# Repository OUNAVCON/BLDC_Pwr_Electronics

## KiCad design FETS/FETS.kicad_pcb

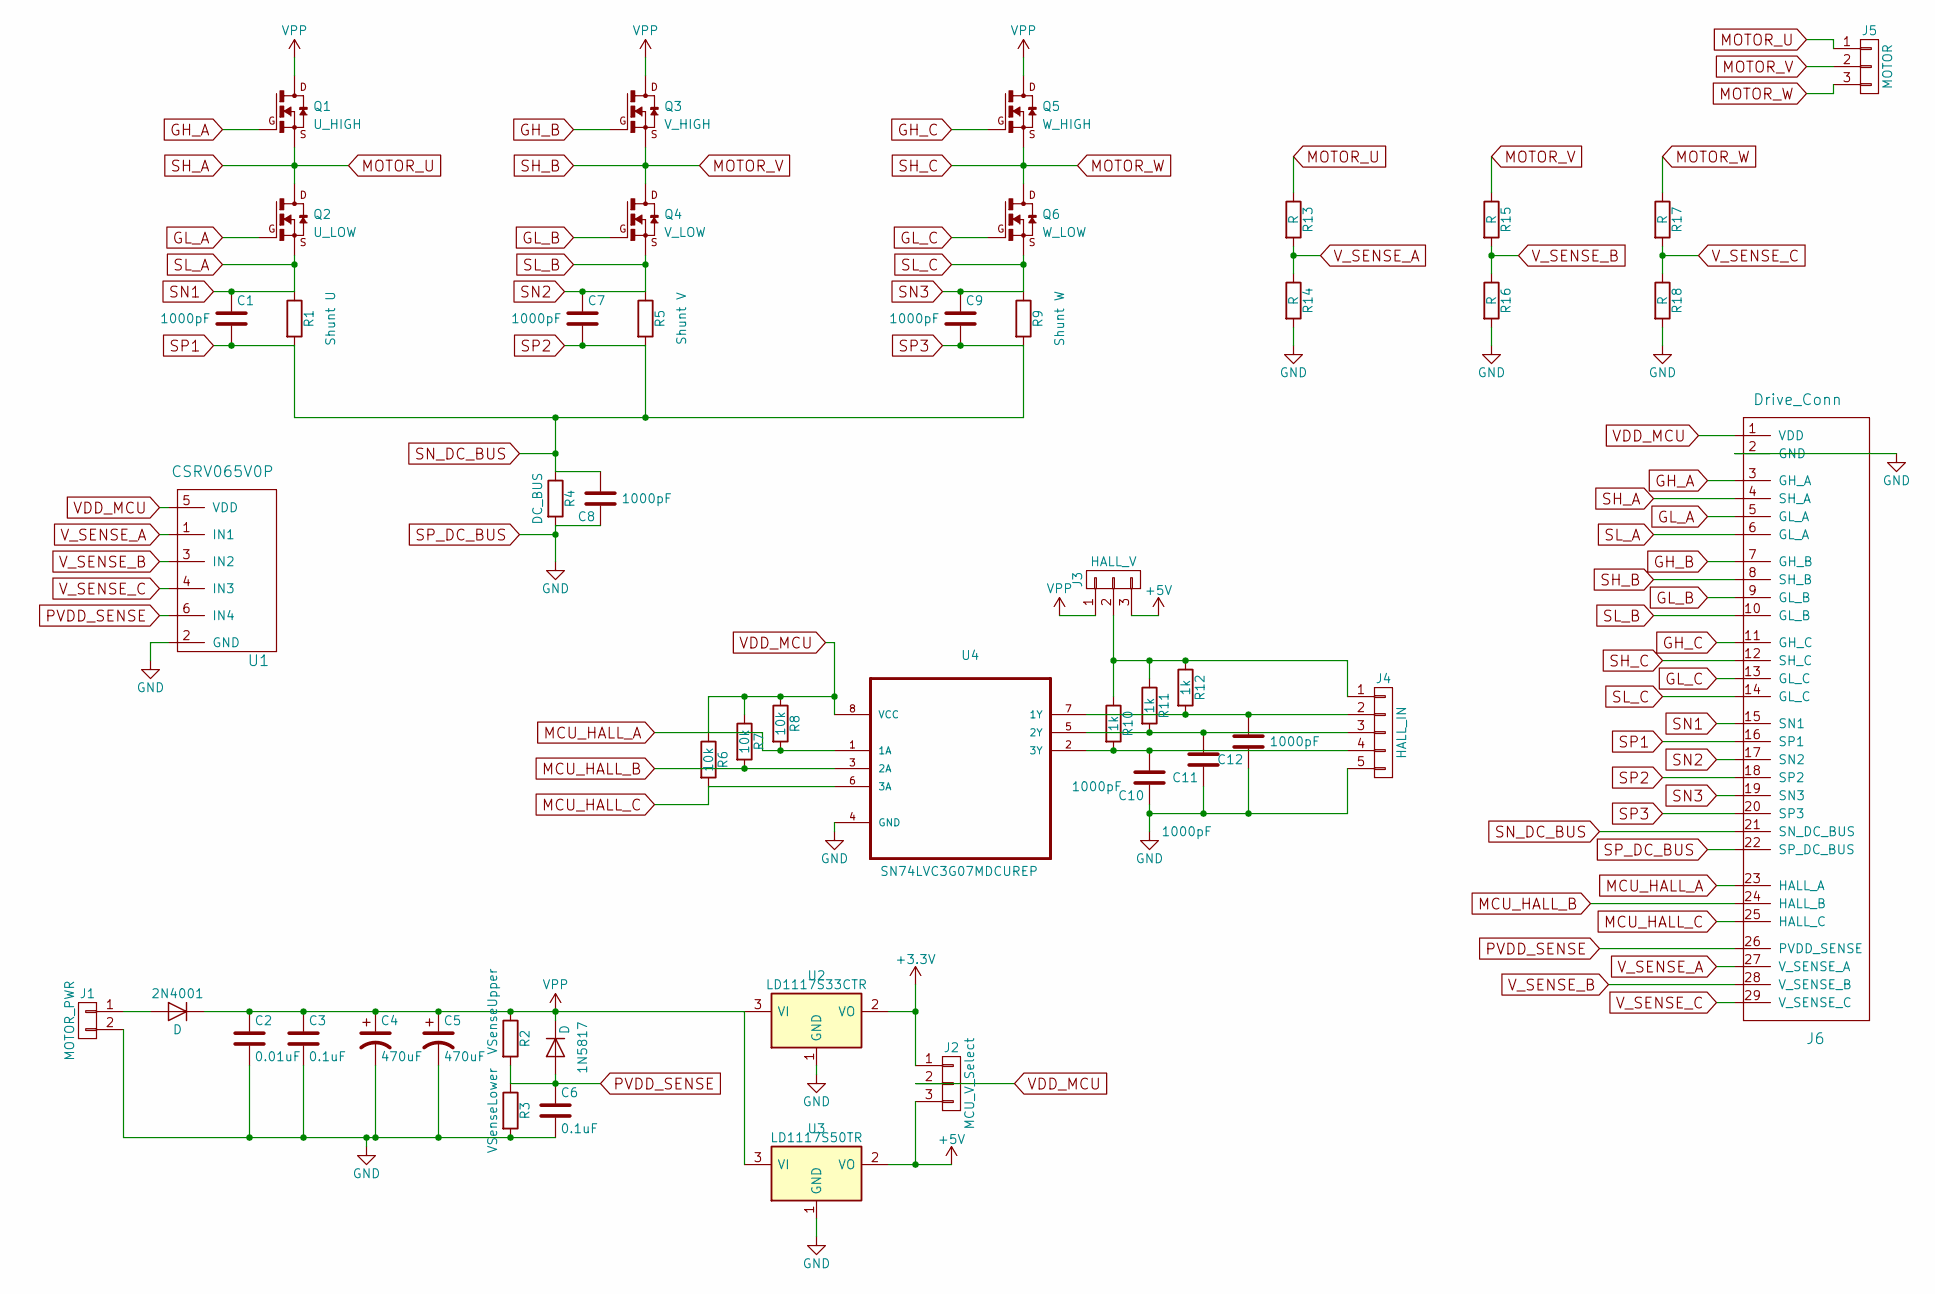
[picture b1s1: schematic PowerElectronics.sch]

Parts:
1N5817, 2N4001: D; D_SMA-SMB_Universal_Handsoldering
C1, C7, C8, C9, C10, C11, C12: 1000pF; C_1206_HandSoldering
C2: 0.01uF; C_1206_HandSoldering
C3, C6: 0.1uF; C_1206_HandSoldering
C4, C5: 470uF; CP_Elec_10x10.5
J1: MOTOR_PWR; Pin_Header_Straight_1x02_Pitch2.54mm
J2: MCU_V_Select; Pin_Header_Straight_1x03_Pitch2.54mm
J3: HALL_V; Pin_Header_Straight_1x03_Pitch2.54mm
J4: HALL_IN; Pin_Header_Straight_1x05_Pitch2.54mm
J5: MOTOR; Pin_Header_Straight_1x03_Pitch2.54mm
J6: Drive_Conn; Pin_Header_Straight_1x29_Pitch2.54mm
Q1: U_HIGH; LFPAK
Q2: U_LOW; LFPAK
Q3: V_HIGH; LFPAK
Q4: V_LOW; LFPAK
Q5: W_HIGH; LFPAK
Q6: W_LOW; LFPAK
R1: Shunt U; R_2512_HandSoldering
R2: VSenseUpper; R_1206_HandSoldering
R3: VSenseLower; R_1206_HandSoldering
R4: DC_BUS; R_2512_HandSoldering
R5: Shunt V; R_2512_HandSoldering
R6, R7, R8: 10k; R_1206_HandSoldering
R9: Shunt W; R_2512_HandSoldering
R10, R11, R12: 1k; R_1206_HandSoldering
R13, R14, R15, R16, R17, R18: R; R_1206_HandSoldering
U1: CSRV065V0P; SOT-363
U2: LD1117S33CTR; SOT-223
U3: LD1117S50TR; SOT-223
U4: SN74LVC3G07MDCUREP; SOP50P310X90-8N

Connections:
+3V3: J2.1, U2.2 (VO)
+5V: J2.3, J3.3, U3.2 (VO)
GH_A: J6.3 (GH_A), Q1.4 (G)
GH_B: J6.7 (GH_B), Q3.4 (G)
GH_C: J6.11 (GH_C), Q5.4 (G)
GL_A: J6.5 (GL_A), Q2.4 (G)
GL_B: J6.9 (GL_B), Q4.4 (G)
GL_C: J6.13 (GL_C), Q6.4 (G)
MCU_HALL_A: J6.23 (HALL_A), R8.2, U4.1 (1A)
MCU_HALL_B: J6.24 (HALL_B), R7.2, U4.3 (2A)
MCU_HALL_C: J6.25 (HALL_C), R6.2, U4.6 (3A)
MOTOR_U: J5.1, J6.4 (SH_A), Q1.1 (S), Q1.2 (S), Q1.3 (S), Q2.5 (D), R13.1
MOTOR_V: J5.2, J6.8 (SH_B), Q3.1 (S), Q3.2 (S), Q3.3 (S), Q4.5 (D), R15.1
MOTOR_W: J5.3, J6.12 (SH_C), Q5.1 (S), Q5.2 (S), Q5.3 (S), Q6.5 (D), R17.1
unnamed: 2N4001.2 (A), J1.1
unnamed: C10.2, J4.4, R10.2, U4.2 (3Y)
unnamed: C11.2, J4.3, R11.2, U4.5 (2Y)
unnamed: C12.2, J4.2, R12.2, U4.7 (1Y)
unnamed: J3.2, J4.1, R10.1, R11.1, R12.1
PVDD_SENSE: 1N5817.2 (A), C6.1, J6.26 (PVDD_SENSE), R2.2, R3.1, U1.6 (IN4)
SL_A: C1.1, J6.6 (GL_A), J6.15 (SN1), Q2.1 (S), Q2.2 (S), Q2.3 (S), R1.1
SL_B: C7.1, J6.10 (GL_B), J6.17 (SN2), Q4.1 (S), Q4.2 (S), Q4.3 (S), R5.1
SL_C: C9.1, J6.14 (GL_C), J6.19 (SN3), Q6.1 (S), Q6.2 (S), Q6.3 (S), R9.1
SN_DC_BUS: C1.2, C7.2, C8.2, C9.2, J6.16 (SP1), J6.18 (SP2), J6.20 (SP3), J6.21 (SN_DC_BUS), R1.2, R4.1, R5.2, R9.2
SP_DC_BUS: C2.2, C3.2, C4.2, C5.2, C6.2, C8.1, C10.1, C11.1, C12.1, J1.2, J4.5, J6.2 (GND), J6.22 (SP_DC_BUS), R3.2, R4.2, R14.2, R16.2, R18.2, U1.2 (GND), U2.1 (GND), U3.1 (GND), U4.4 (GND)
VDD_MCU: J2.2, J6.1 (VDD), R6.1, R7.1, R8.1, U1.5 (VDD), U4.8 (VCC)
VPP: 1N5817.1 (K), 2N4001.1 (K), C2.1, C3.1, C4.1, C5.1, J3.1, Q1.5 (D), Q3.5 (D), Q5.5 (D), R2.1, U2.3 (VI), U3.3 (VI)
V_SENSE_A: J6.27 (V_SENSE_A), R13.2, R14.1, U1.1 (IN1)
V_SENSE_B: J6.28 (V_SENSE_B), R15.2, R16.1, U1.3 (IN2)
V_SENSE_C: J6.29 (V_SENSE_C), R17.2, R18.1, U1.4 (IN3)

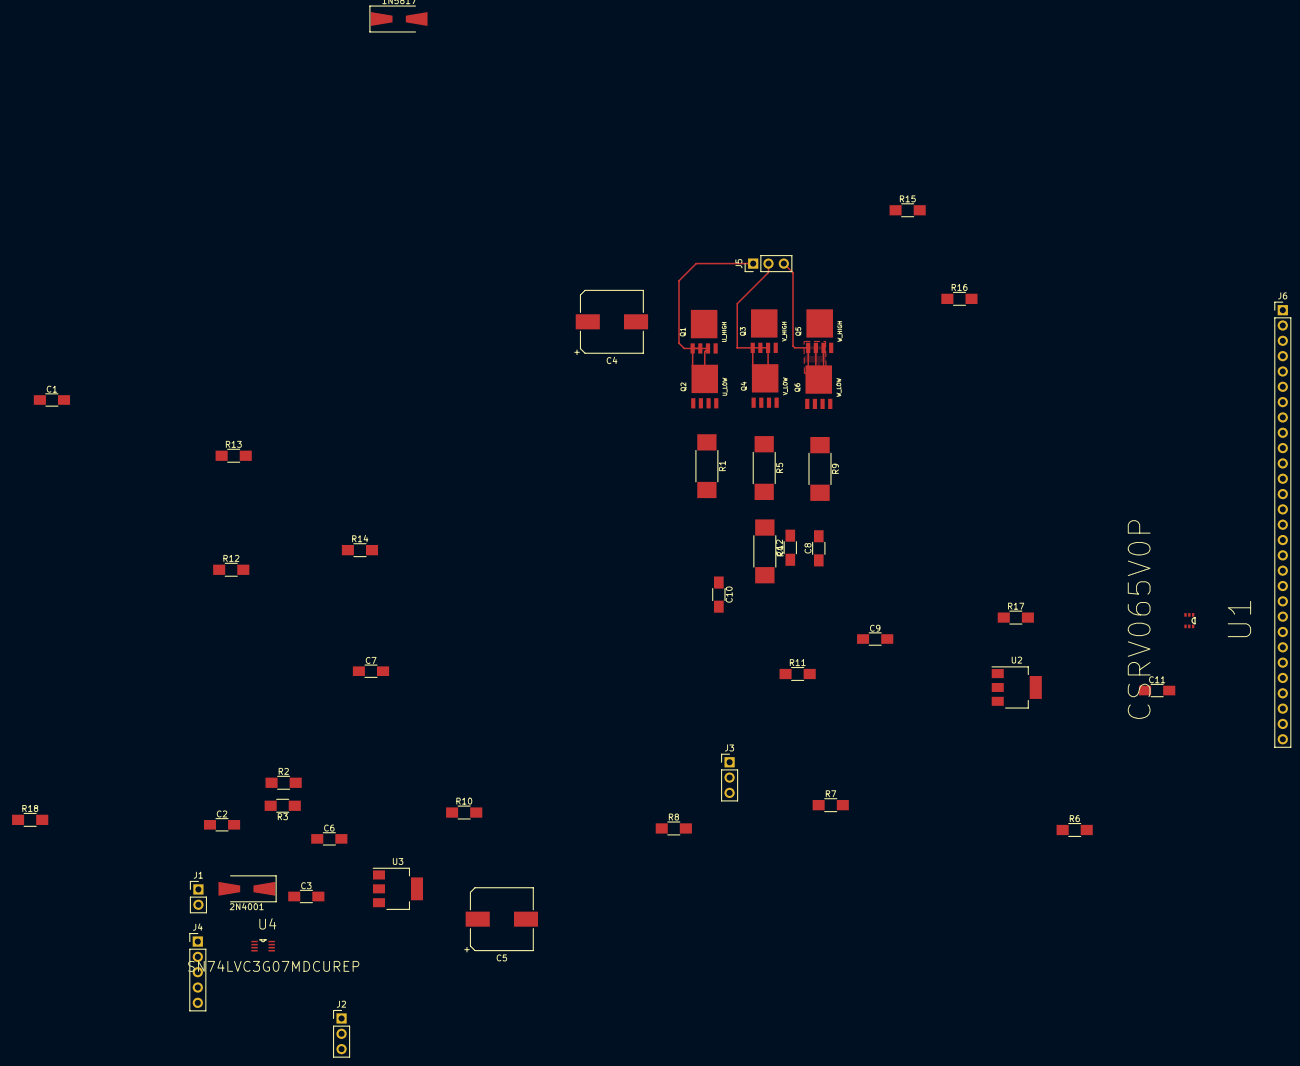
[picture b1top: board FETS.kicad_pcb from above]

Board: 2 copper layers, 48 parts (0 on the bottom side), 30 nets.

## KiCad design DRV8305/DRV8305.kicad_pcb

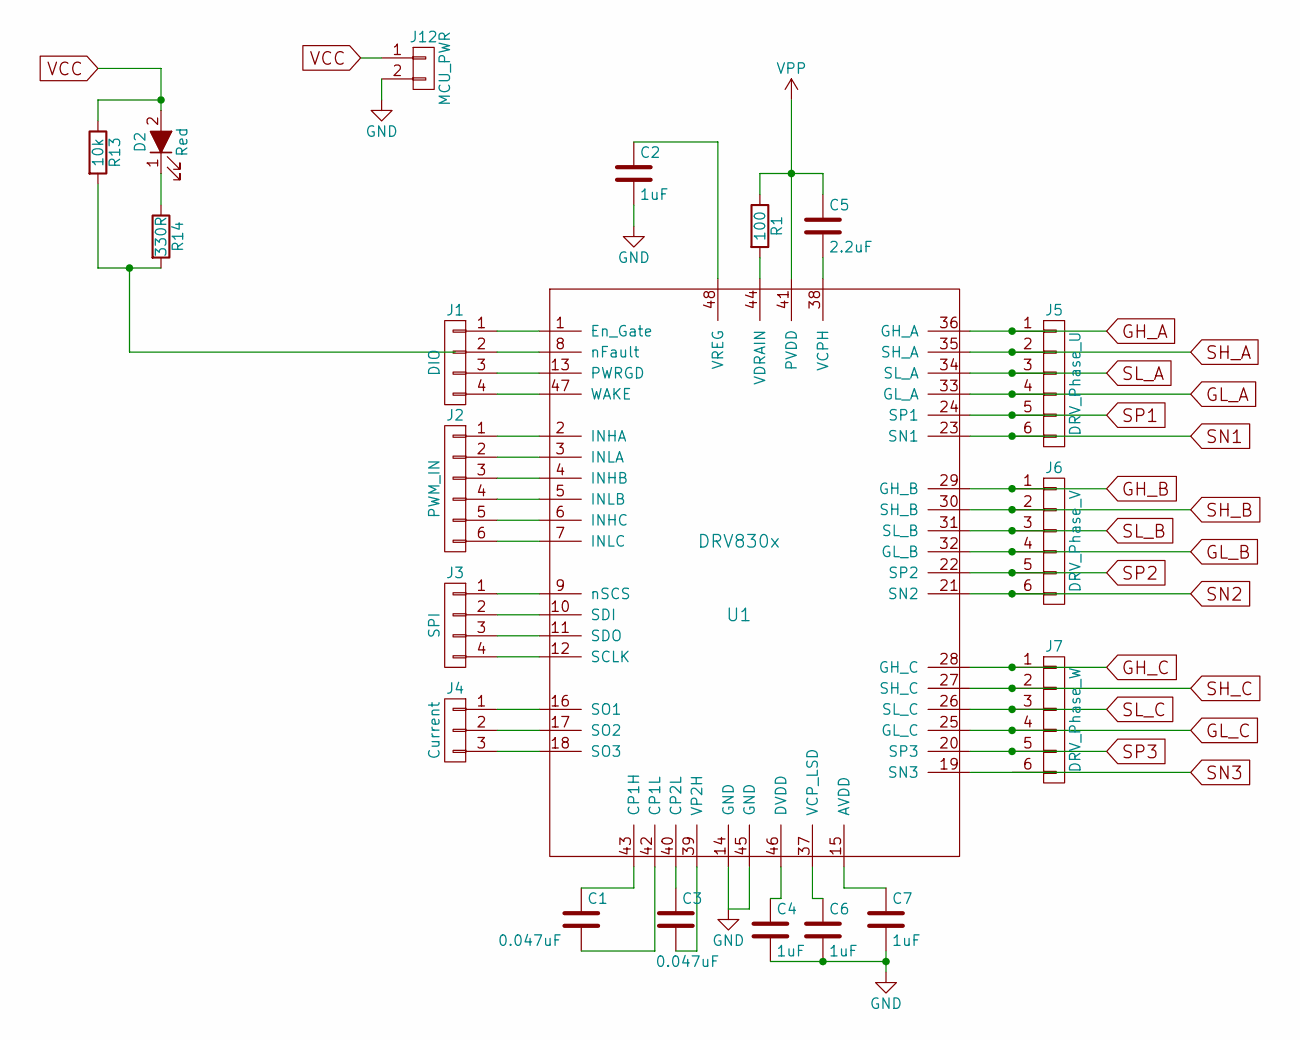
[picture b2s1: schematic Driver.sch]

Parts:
C1, C3: 0.047uF; C_1206_HandSoldering
C2, C4, C6, C7: 1uF; C_1206_HandSoldering
C5: 2.2uF; C_1206_HandSoldering
D2: Red; LED_1206_HandSoldering
J1: DIO; Pin_Header_Straight_1x04_Pitch2.54mm
J2: PWM_IN; Pin_Header_Straight_1x06_Pitch2.54mm
J3: SPI; Pin_Header_Straight_1x04_Pitch2.54mm
J4: Current; Pin_Header_Straight_1x03_Pitch2.54mm
J5: DRV_Phase_U; Pin_Header_Straight_1x06_Pitch2.54mm
J6: DRV_Phase_V; Pin_Header_Straight_1x06_Pitch2.54mm
J7: DRV_Phase_W; Pin_Header_Straight_1x06_Pitch2.54mm
J12: MCU_PWR; Pin_Header_Straight_1x02_Pitch2.54mm
R1: 100; R_1206_HandSoldering
R13: 10k; R_1206_HandSoldering
R14: 330R; R_1206_HandSoldering
U1: DRV830x; QFP50P900X900X120-49N

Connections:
GH_A: J5.1, U1.36 (GH_A); also elsewhere on the board
GH_B: J6.1, U1.29 (GH_B); also elsewhere on the board
GH_C: J7.1, U1.28 (GH_C); also elsewhere on the board
GL_A: J5.4, J5.6, J6.4, J6.6, J7.4, U1.19 (SN3), U1.21 (SN2), U1.23 (SN1), U1.25 (GL_C), U1.32 (GL_B), U1.33 (GL_A); also elsewhere on the board
GND: C2.2, C4.2, C6.2, C7.2, J12.2, U1.14 (GND), U1.45 (GND); also elsewhere on the board
MOTOR_U: J5.2, U1.35 (SH_A); also elsewhere on the board
MOTOR_V: J6.2, U1.30 (SH_B); also elsewhere on the board
MOTOR_W: J7.2, U1.27 (SH_C); also elsewhere on the board
unnamed: C1.1, U1.43 (CP1H)
unnamed: C1.2, U1.42 (CP1L)
unnamed: C2.1, U1.48 (VREG)
unnamed: C3.1, U1.40 (CP2L)
unnamed: C3.2, U1.39 (VP2H)
unnamed: C4.1, U1.46 (DVDD)
unnamed: C5.2, U1.38 (VCPH)
unnamed: C6.1, U1.37 (VCP_LSD)
unnamed: C7.1, U1.15 (AVDD)
unnamed: D2.1 (K), R14.1
unnamed: J1.1, U1.1 (En_Gate)
unnamed: J1.2, U1.8 (nFault)
unnamed: J1.3, U1.13 (PWRGD)
unnamed: J1.4, U1.47 (WAKE)
unnamed: J2.1, U1.2 (INHA)
unnamed: J2.2, U1.3 (INLA)
unnamed: J2.3, U1.4 (INHB)
unnamed: J2.4, U1.5 (INLB)
unnamed: J2.5, U1.6 (INHC)
unnamed: J2.6, U1.7 (INLC)
unnamed: J3.1, U1.9 (nSCS)
unnamed: J3.2, U1.10 (SDI)
unnamed: J3.3, U1.11 (SDO)
unnamed: J3.4, U1.12 (SCLK)
unnamed: J4.1, U1.16 (SO1)
unnamed: J4.2, U1.17 (SO2)
unnamed: J4.3, U1.18 (SO3)
unnamed: R1.2, U1.44 (VDRAIN)
unnamed: R13.2, R14.2
SL_A: J5.3, U1.34 (SL_A)
SL_B: J6.3, U1.31 (SL_B)
SL_C: J7.3, U1.26 (SL_C)
SP1: J5.5, U1.24 (SP1)
SP2: J6.5, U1.22 (SP2)
SP3: J7.5, U1.20 (SP3)
VCC: D2.2 (A), J12.1, R13.1; also elsewhere on the board
VPP: C5.1, R1.1, U1.41 (PVDD); also elsewhere on the board

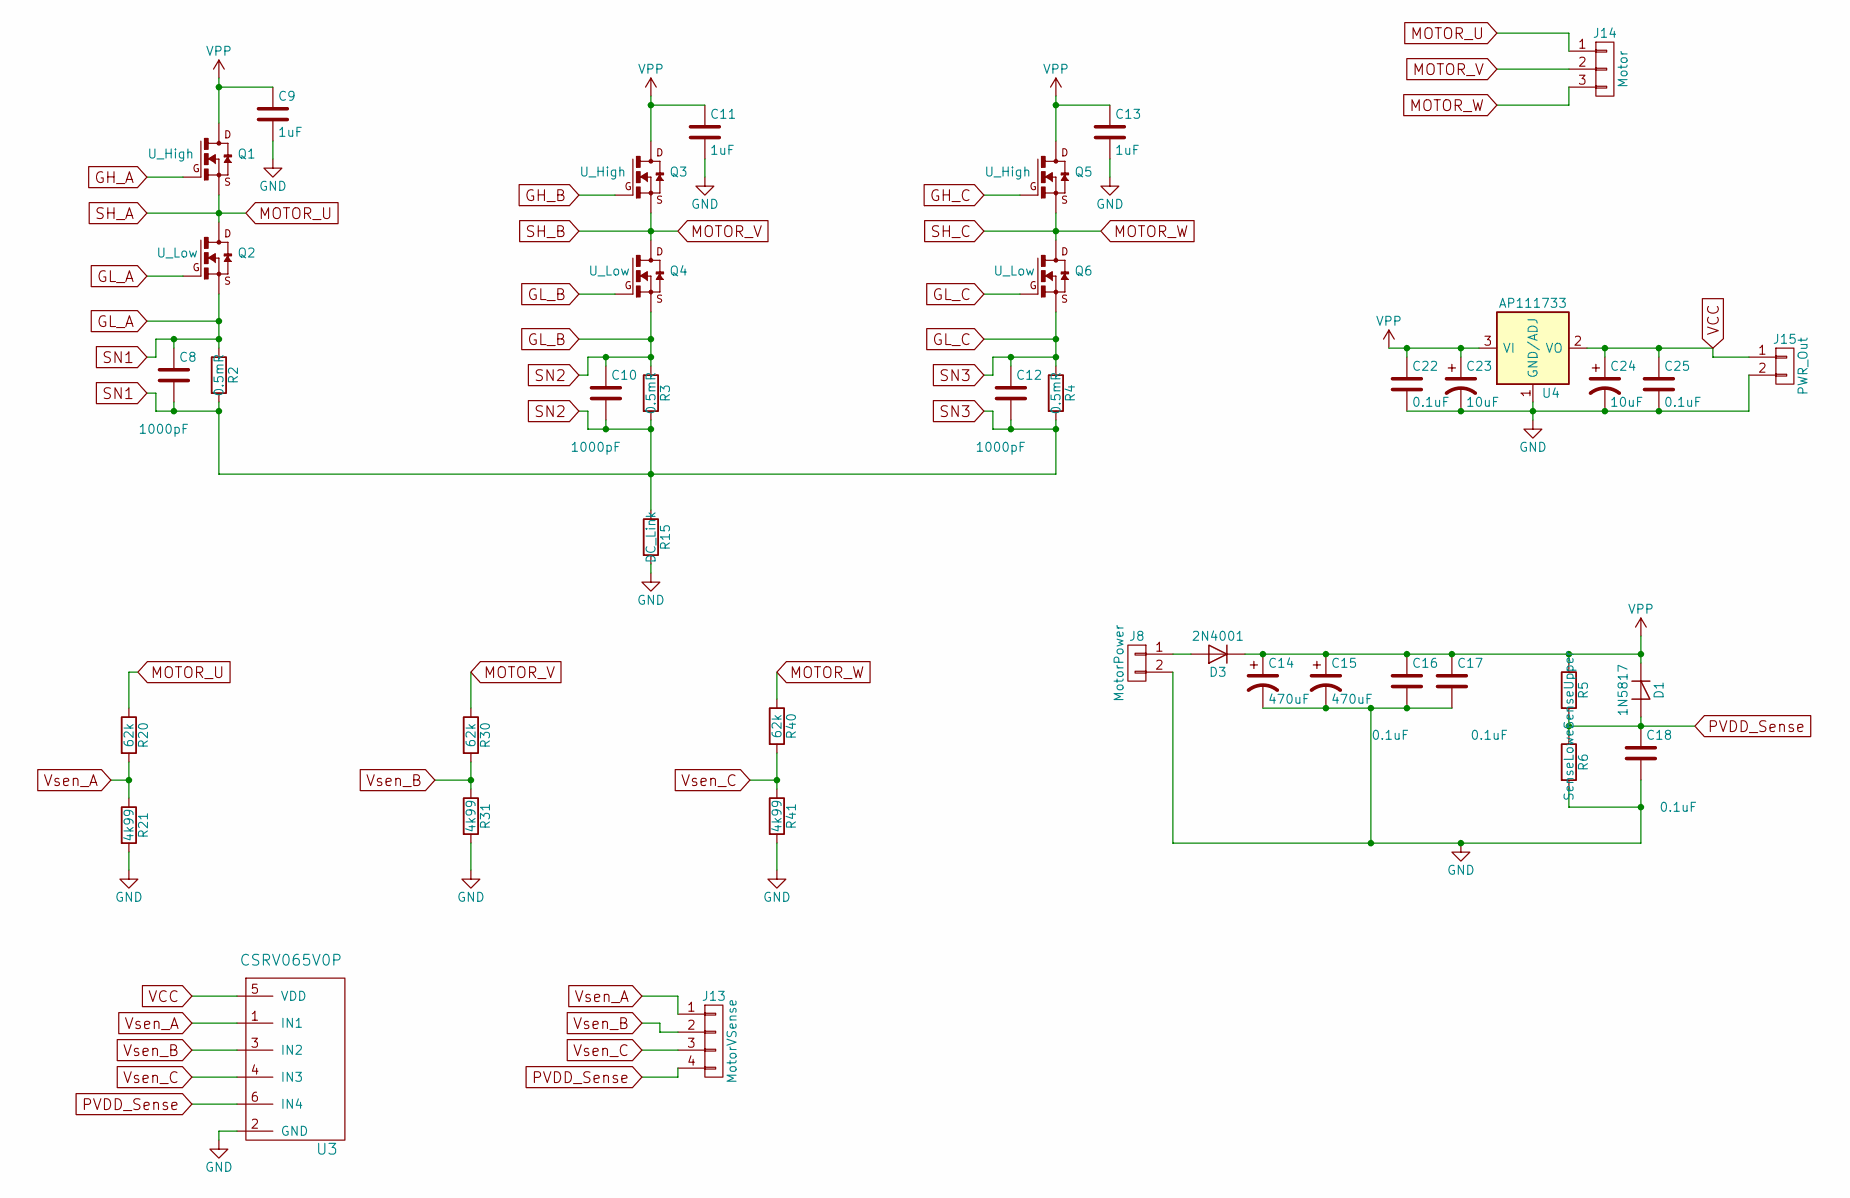
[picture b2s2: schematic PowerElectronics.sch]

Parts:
C8, C10, C12: 1000pF; C_1206_HandSoldering
C9, C11, C13: 1uF; C_1206_HandSoldering
C14, C15: 470uF; CP_Elec_4x5.3
C16, C17, C18, C22, C25: 0.1uF; C_1206_HandSoldering
C23, C24: 10uF; CP_Elec_4x5.3
D1: 1N5817; D_SMA_Handsoldering
D3: 2N4001; D_SMA_Handsoldering
J8: MotorPower; Pin_Header_Straight_1x02_Pitch2.54mm
J13: MotorVSense; Pin_Header_Straight_1x04_Pitch2.54mm
J14: Motor; Pin_Header_Straight_1x03_Pitch2.54mm
J15: PWR_Out; Pin_Header_Straight_1x02_Pitch2.54mm
Q1, Q3, Q5: U_High; LFPAK
Q2, Q4, Q6: U_Low; LFPAK
R2, R3, R4: 0.5mR; R_2512_HandSoldering
R5: SenseUpper; R_1206_HandSoldering
R6: SenseLower; R_1206_HandSoldering
R15: DC_Link; R_2512_HandSoldering
R20, R30, R40: 62k; R_1206_HandSoldering
R21, R31, R41: 4k99; R_1206_HandSoldering
U3: CSRV065V0P; SOT-363
U4: AP111733; SOT-223

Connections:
GH_A: Q1.4 (G); also elsewhere on the board
GH_B: Q3.4 (G); also elsewhere on the board
GH_C: Q5.4 (G); also elsewhere on the board
GL_A: C8.1, C8.2, C10.1, C10.2, C12.1, C12.2, Q2.1 (S), Q2.2 (S), Q2.3 (S), Q2.4 (G), Q4.1 (S), Q4.2 (S), Q4.3 (S), Q4.4 (G), Q6.1 (S), Q6.2 (S), Q6.3 (S), Q6.4 (G), R2.1, R2.2, R3.1, R3.2, R4.1, R4.2, R15.1; also elsewhere on the board
GND: C9.2, C11.2, C13.2, C14.2, C15.2, C16.2, C17.2, C18.2, C22.2, C23.2, C24.2, C25.2, J8.2, J15.2, R6.2, R15.2, R21.2, R31.2, R41.2, U3.2 (GND), U4.1 (GND/ADJ); also elsewhere on the board
MOTOR_U: J14.1, Q1.1 (S), Q1.2 (S), Q1.3 (S), Q2.5 (D), R20.1; also elsewhere on the board
MOTOR_V: J14.2, Q3.1 (S), Q3.2 (S), Q3.3 (S), Q4.5 (D), R30.1; also elsewhere on the board
MOTOR_W: J14.3, Q5.1 (S), Q5.2 (S), Q5.3 (S), Q6.5 (D), R40.1; also elsewhere on the board
unnamed: D3.2 (A), J8.1
PVDD_Sense: C18.1, D1.2 (A), J13.4, R5.2, R6.1, U3.6 (IN4)
VCC: C24.1, C25.1, J15.1, U3.5 (VDD), U4.2 (VO), U4.4 (VO); also elsewhere on the board
VPP: C9.1, C11.1, C13.1, C14.1, C15.1, C16.1, C17.1, C22.1, C23.1, D1.1 (K), D3.1 (K), Q1.5 (D), Q3.5 (D), Q5.5 (D), R5.1, U4.3 (VI); also elsewhere on the board
Vsen_A: J13.1, R20.2, R21.1, U3.1 (IN1)
Vsen_B: J13.2, R30.2, R31.1, U3.3 (IN2)
Vsen_C: J13.3, R40.2, R41.1, U3.4 (IN3)

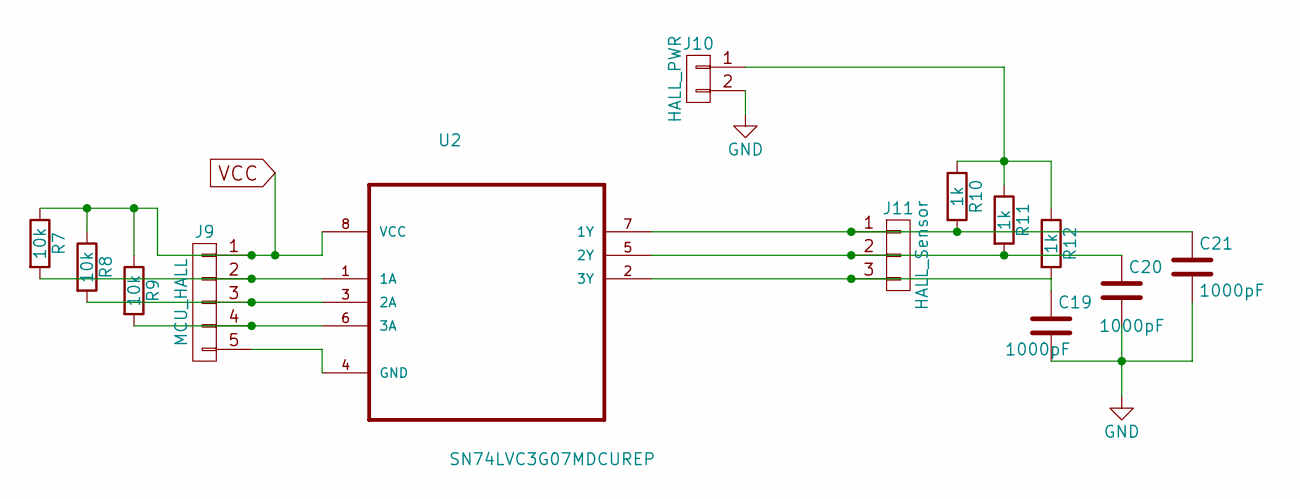
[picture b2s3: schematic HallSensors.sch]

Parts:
C19, C20, C21: 1000pF; C_1206_HandSoldering
J9: MCU_HALL; Pin_Header_Straight_1x05_Pitch2.54mm
J10: HALL_PWR; Pin_Header_Straight_1x02_Pitch2.54mm
J11: HALL_Sensor; Pin_Header_Straight_1x03_Pitch2.54mm
R7, R8, R9: 10k; R_1206_HandSoldering
R10, R11, R12: 1k; R_1206_HandSoldering
U2: SN74LVC3G07MDCUREP; SOP50P310X90-8N

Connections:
GND: C19.2, C20.2, C21.2, J10.2; also elsewhere on the board
unnamed: C19.1, J11.3, R12.2, U2.2 (3Y)
unnamed: C20.1, J11.2, R11.2, U2.5 (2Y)
unnamed: C21.1, J11.1, R10.2, U2.7 (1Y)
unnamed: J9.2, R7.2, U2.1 (1A)
unnamed: J9.3, R8.2, U2.3 (2A)
unnamed: J9.4, R9.2, U2.6 (3A)
unnamed: J9.5, U2.4 (GND)
unnamed: J10.1, R10.1, R11.1, R12.1
VCC: J9.1, R7.1, R8.1, R9.1, U2.8 (VCC); also elsewhere on the board

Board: 2 copper layers, 74 parts (0 on the bottom side), 58 nets, no tracks yet.

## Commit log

2018-03-15 Added first layout
2018-03-15 Seperated out BLDC
2018-03-19 Added MCP8026 lib
